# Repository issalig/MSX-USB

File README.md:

# MSX-USB
## My fork and DIY guide
My fork provides a minified version of the pcb with PLC sockets and a header expansion as well as detailed building guide. All the other things are the same as original S0urceror version (https://github.com/S0urceror/MSX-USB) and I send him lots of thanks for sharing his knowledge.

As I built the cartridge from the scratch I will tell you some of the problems I faced and happily solved out.

### Step 0: Make a PCB
When I saw original S0urceror design I thought that maybe using PLC sockets could make the pcb smaller, then I tried to shrink everything into the minimum space with the maximum capabilities and that's why I added a expansion header. I am using https://www.kicad.org/ for the PCB layout and https://freerouting.org/ for the routing. I find freerouting extremely useful since there are a lot of connections and a small place to do the job. Sometines freerouting does not find the solution and you need to finish it manually. If this happens you can also lower clearance matrix values down to 125-150. Also using freerouting allows you to change the location of components without the need to re-route everything again.

Last version of the pcb is kicad-cpld-mini-v2 (ch376 is in front but still *untested*) and kicad-cpld-mini (ch376 is in the back side and *tested ok*).  Of course if you are satisfied with my design just can just use the files provided. Otherwise you can improve the design and share it.

### Step 1: Program CPLD
You will need the obsolete part EPM7064SLC44, the important part here is **SLC**, EPM7064SLC44-10 is also valid. You can get them from ali and other places but as they are refurbished/recovered from dumpsters expect to have only 50% working, so order double. Here is a possible link https://aliexpress.com/item/1005001512009032.html but there is a myriad of sellers.
Then, you will need a programmer such as USB blaster. I got this one https://aliexpress.com/item/1005002674193901.html
Next, you have to download Quartus software version **13.0sp1**, as newer versions do not support EPM7064. Go to https://fpgasoftware.intel.com/?edition=lite and proceed with the download and installation.

If you are in linux like me you will  need to add the this rules to file /etc/udev/rules.d/37-usbblaster.rules
```
SUBSYSTEM=="usb", ATTRS{idVendor}=="09fb", ATTRS{idProduct}=="6001", GROUP="plugdev", MODE="0666", SYMLINK+="usbblaster" 
```
and then restart the service
```
sudo service udev restart 
```

Connect the programmer to the board and also **power the board externally with 5V**, you can do it using the expansion header or CH3786 header. Find the pins VCC and GND and you are done. Failing to do so it will result in an JTAG read error.

Next, we check your connection and if everything went ok you will see this message.
```
$ ./quartus_pgm --auto
Info (213045): Using programming cable "USB-Blaster [3-1]"
1) USB-Blaster [3-1]
  070640DD   EPM7064S

Info: Quartus II 32-bit Programmer was successful. 0 errors, 0 warnings
    Info: Peak virtual memory: 127 megabytes
    Info: Processing ended: Sat Dec 18 10:16:56 2021
    Info: Elapsed time: 00:00:00
    Info: Total CPU time (on all processors): 00:00:00
```

And it has arrived the amazing moment where you are going to program it (you can do it with the command line *quartus_pgm* or with the GUI tool *quartus*)
with the following file https://github.com/S0urceror/MSX-USB/blob/master/hardware/quartus/output_files/MSXUSB.pof
```
./quartus_pgm -m jtag -o "p;./MSXUSB.pof"
```

In case the devices still shows JTAG communication error, keep calm and go to the next step.

### Step 1b. Recovering deaf JTAG units
It happens that some of the refurbished units come with programs that used JTAG pins for I/O and they are not able to be used for JTAG. I threw some of them to the bin until I discovered a recovery process (https://www.eevblog.com/forum/fpga/atmel-atf150x-cpld-and-wincupl/msg3162224/#msg3162224).
- Apply 12V to CPLD pin OE1 (44) with a 2k2 resistor for a minute or so. In my pcb you can access OE1 pin on header pin 15 (RST).
- Disconnect 12V, connect 5V and try to program it.
- Hopefully some CPLD's are working now! 

### Step 1c. Use an still in production CPLD, use a ATF1504AS
As seen in https://www.eevblog.com/forum/fpga/atmel-atf150x-cpld-and-wincupl/msg3113922/#msg3113922 ATF1504AS is pin compatible to EPM7064 and it is a valid replacement for EPM7064.
The changes are not that big: we will need to convert .pof into .jed and then into .svf.

I compiled the following info from different sources https://github.com/marqs85/snes_dejitter/blob/master/README.md, https://github.com/SukkoPera/OpenAmiga500FastRamExpansion/blob/master/firmware/README.md and https://www.hackup.net/2020/01/erasing-and-programming-the-atf1504-cpld/

All the resources for ATMEL CPLDS can be found at https://www.microchip.com/en-us/products/fpgas-and-plds/spld-cplds/pld-design-resources

First we need to download pof2jef from http://ww1.microchip.com/downloads/archive/pof2jed.zip
Then in winpof2jed.exe (yes it works with wine in linux :))
```
1. Select .pof file from previous step as input file
2. Select 1504AS as device
3. Change the following options:
  * Reduce MC power -> On
  * Open Collector -> Off
  * JTAG mode -> On
  * Slew rate -> Slow
4. Click "Run"
```

The important thing here is JTAG Mode **ON**, if you are wrong you will block JTAG but don't panic, we already know that applying 12V it will be enabled again.

Once we have the .jed file it is time to generate svf with ATMISP that you can download it from http://ww1.microchip.com/downloads/en/DeviceDoc/ATMISP7.zip. Then, you should follow these steps.

```
1. Create a new device chain via File->New
2. Set number of devices to 1
3. Set device to ATF1504AS
4. Set JTAG instruction to "Program/Verify"
5. Select .jed file from previous step as JEDEC file
6. Name your svf file
7. Click "OK"
8. Tick "Write SVF file" and click "Run"
```

We are almost there. We just need to flash it with openocd

But first we need the config file for usbblaster and you can save it as altera-usb-blaster.cfg
```
#
# Altera USB-Blaster
#
# http://www.altera.com/literature/ug/ug_usb_blstr.pdf
#

interface usb_blaster
usb_blaster_lowlevel_driver ftdi
# These are already the defaults.
# usb_blaster_vid_pid 0x09FB 0x6001
# usb_blaster_device_desc "USB-Blaster"
adapter_khz 3000
```

And this is the magical line that will flash your CPLD (Do not forget to power usbblaster with external 5V)

```
 openocd -f altera-usb-blaster.cfg -c "adapter_khz 400" -c "transport select jtag" -c "jtag newtap ATF1504AS tap -irlen 3 -expected-id 0x0150403f" -c init -c "svf msxusb.svf" -c "sleep 200" -c shutdown
 ```
 
If everything went ok you will see something ending like this

```
Time used: 0m12s613ms 
svf file programmed successfully for 3299 commands with 0 errors
shutdown command invoked

```

### Step 2. Flash memory
Recommended memory chips is SST39SF040 (512kb) but I also managed to make it work with SST39SF020 (256kb). Then, you will need a programmer such as TL866 II https://aliexpress.com/item/33000308958.html and the file we will write is located at https://github.com/S0urceror/MSX-USB/blob/master/drivers/NextorUsbHost/dist/nextor.rom

If you prefer to use a command line tool I suggest you minipro https://gitlab.com/DavidGriffith/minipro

```
$ ./minipro --device SST39SF040@PLCC32 --write nextor.rom -s
Found TL866II+ 04.2.126 (0x27e)
Warning: Firmware is newer than expected.
  Expected  04.2.124 (0x27c)
  Found     04.2.126 (0x27e)
Chip ID OK: 0xBFB7
Warning: Incorrect file size: 131072 (needed 524288)
Erasing... 0.40Sec OK
Writing Code...  26.38Sec  OK
Reading Code...  4.00Sec  OK
Verification OK

```

### Step 3. Select a valid USB drive
Not all USB drives will work :(, I have detected that the ones with the following EnpointAddress values usually work. It will probably work if you have the values shown below. If you find other values, please report.
```
lsusb -v | grep bEndpointAddress
...
bEndpointAddress 0x01 EP 1 OUT
bEndpointAddress 0x82 EP 2 IN 
```

### Step 4. Prepare a disk
Once we are here, all the hardware requirements are fulfilled, yes, you can go for a beer now!
It is only a matter of creating a disk image with the system files provided at https://github.com/S0urceror/MSX-USB/tree/master/software/dist

- If you have a MSX1 (i.e. VG8020, ...) you will be limited to 720kb disks and FAT12. Do not complain, do you still prefer a slow datacorder?
To create a MSX disk image I use dsktool from https://github.com/nataliapc/MSX_devs/tree/master/dsktool

I also provide linux and windows version of dsktool in order to make it easier, you can get them at https://github.com/issalig/MSX-USB/tree/master/software/utils
```
#create disk
dsktool c MYDISK.DSK
#add system files
dsktool a MYDISK.DSK COMMAND.COM MSXDOS.SYS
#add other files
dsktool a MYDISK.DSK MYGAME.COM
```
In case you prefer a GUI program you can also use DiskMgr http://www.lexlechz.at/en/software/DiskMgr.html

Next, flash it. **Warning: check if your device is /dev/sda** or you will destroy something. If you are a windows user maybe Rufus can write the image, if it works, please report it. 

```
sudo dd if=MYDISK.DSK of=/dev/sda
```

- If you are a lucky MSX2 owner you will need a FAT16 partition of 16Mb with COMMAND2.COM and NEXTOR.SYS.

In Linux I have created an image available at https://github.com/issalig/MSX-USB/blob/master/software/utils/msx2.zip. You can do it with the following commands.
```
#create a 16 Mb disk and format it to FAT16
sudo  dd if=/dev/zero of=msx2.dsk bs=1024 count=16k
sudo mkfs.fat -F 16 msx2.dsk

#mount it
mkdir 16mb 
sudo mount -o loop msx2.dsk 16mb/

#copy all the stuff
sudo cp COMMAND2.COM NEXTOR.SYS 16mb

#unmount it and flash it
sudo umount 16mb
sudo dd if=msx2.dsk of=/dev/sda bs=16M
```
Unplug the stick from the computer, plug it in the msxusb, switch on the MSX and you are in. **Enjoy!**

As usual report how is it done with windows (maybe mini partition tool can help but I have never tried it).

## Some history
In the 80's the MSX standard was created by Kazuhiko Nishi. He envisioned a simple yet powerful home computer based on standard hardware, software (BIOS/MSX DOS) and connectivity. From 1983 to 1990 manufacturers, like Philips, Sony, Yamaha, Sharp, Canon and many more, made computers according to this standard.

Because of the fact that extensibility was part of the standard people could design cartridges that would add synthesizer sound, memory, modems, rom-based games, or combinations of the above.

Cartridges were connected via a standard 50pin connector that remained the same accross 4 generations of MSX (1/2/2+/TurboR). BIOS and MSX-DOS were designed in a way to discover these via rom-based drivers, software hooks, extended bios.

Standardisation offers a big advantage because everything that adheres to the standard can connect to it.

## USB
USB was designed in the 90's to do something similar. To standardize the connection of peripherals to personal computers, both to communicate with and to supply electric power. It has now largely replaced interfaces such as serial ports and parallel ports, and has become commonplace on a wide range of devices. Like USB flash drives, keyboards, mice, wifi, serial, camera's, etc.

What if the MSX would have an USB connection? And if the BIOS/MSX DOS would automatically recognize devices connected to it?

## Meet MSX-USB
Inspired by the work of Xavirompe and his [RookieDrive](http://rookiedrive.com/en/) I set out to do exactly this. And since I'm a big believer of open standards and open source I'm opening up my work to everyone.

On this GitHub page you can find:
* Schematics (KiCAD), that interfaces a cheap USB CH376s board to the MSX cartridge port.
* Drivers, currently Flash drives on Nextor and HID keyboards are supported.
* Debugging tools, to connect a test board to your PC/MAC and assist in debugging.

On my GitHub I also have forks of OpenMSX and CocoaMSX that either emulate or connect to a test board via serial to assist in development and debugging.

## Schematics
This connects the CH376s board you can find on eBay or AliExpress for around 4 Euro to the MSX. 

Circuitry is added to correctly handle the _BUSDIR signal. Make sure you select parallel by setting the jumper on the CH376s board correctly.

The CH376s board will be visible on port 10h and 11h on the MSX. Port 11h is the command port and 10h is the data port. Specifics on how to program for the CH376s are scattered around the Internet:
* https://www.mpja.com/download/ch376ds1.pdf
* https://arduinobasics.blogspot.com/2015/05/ch376s-usb-readwrite-module.html

Most information is available on how to use the higher-order API for flash drives. 

If you want to use other USB devices you have to go low-level. As it turns out Konamiman already did some work there and after some researching I got USB HID Keyboards, Ethernet, Serial working as well. Check out my source-code or these great pages for more information:
* http://www.usbmadesimple.co.uk/index.html
* https://www.beyondlogic.org/usbnutshell/usb1.shtml

## UNAPI USB
I wrote a UNAPI USB specification and implemented the Usb Host driver according to this. The next version of this Host driver will also implement the Usb Hub specification and enumerate and initialise all devices connected.

## USB HID Keyboard
The Usb Keyboard driver connects to Unapi Usb driver and hooks itself to H.CHGE. From that moment on it replaces your trusted MSX keyboard by a shiny new USB Keyboard. Or a wireless one if you have inserted the appropriate Logitech receiver.

## USB CDC ECM Ethernet
The USB CDC ECM Ethernet driver is finished. It uses the Unapi USB and conforms to the Unapi Ethernet standard. Internestor Lite can now connect and use your USB Ethernet device. Please note that currently we only support USB CDC ECM. Make sure your Ethernet device supports this.

All USB Ethernet devices built around the **RTL8153** chipset support USB CDC ECM. They usually cost around 20 euro.

## USB Storage
A low level USB driver is created to connect to storage devices like thumb drives, portable hard disks, etc. 

## USB Hub
The USB Hub driver will interrogate an USB Hub and all devices connected to it.

# Installation instructions
Check [this page](INSTALL.md) for installation instructions and links to the various binaries that have been developed.

# Build your own (DIY)
Check [this page](DIY.md) for information on how to make the PCB, program the CPLD device, flash the ROM, etc.

# Collaboration
Do you want to help with the development of MSX USB? Write drivers for other devices? Or contribute in other ways?

Please drop me line on sourceror at neximus.nl or meet me on the msx.org forum.

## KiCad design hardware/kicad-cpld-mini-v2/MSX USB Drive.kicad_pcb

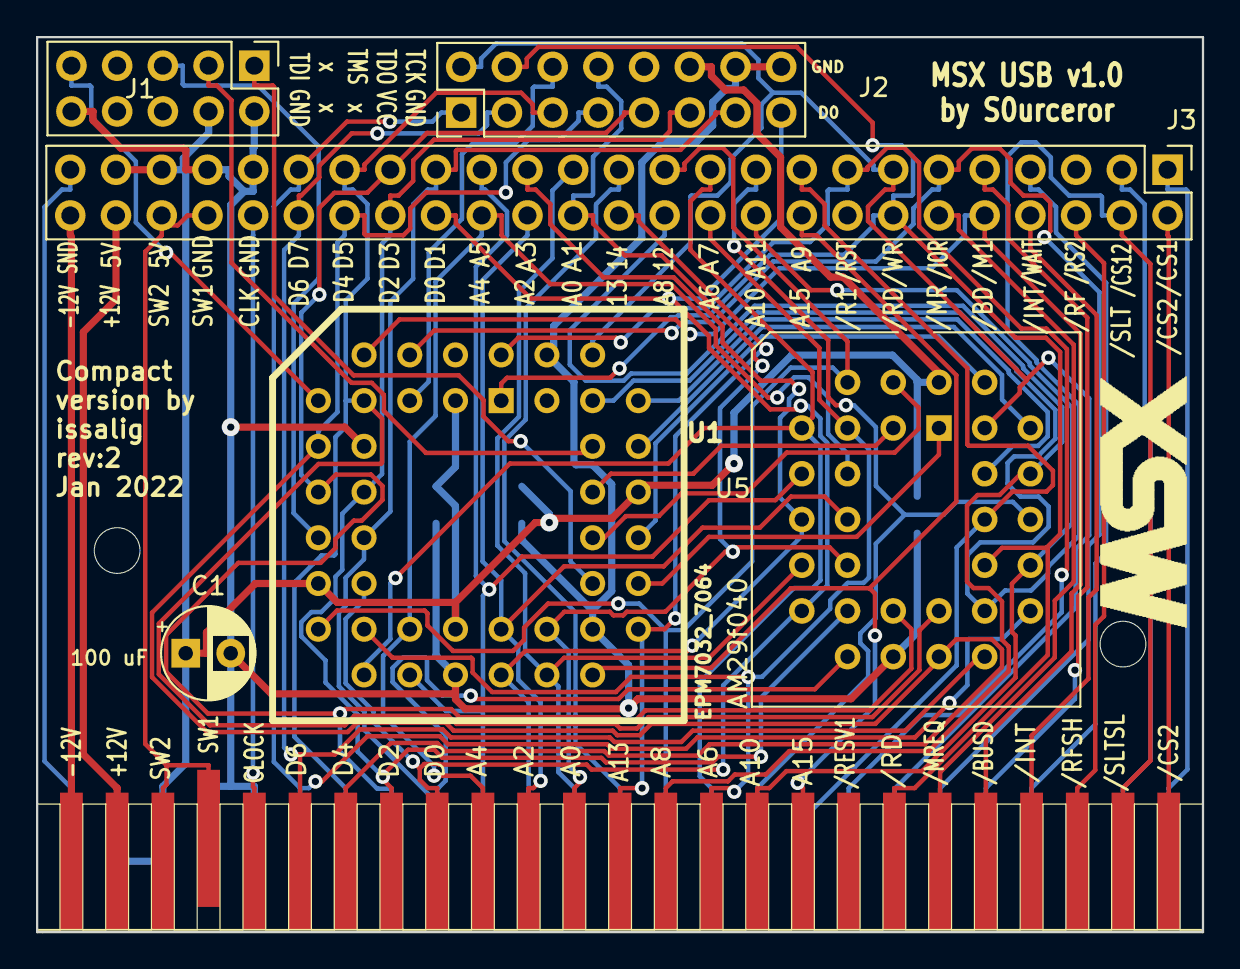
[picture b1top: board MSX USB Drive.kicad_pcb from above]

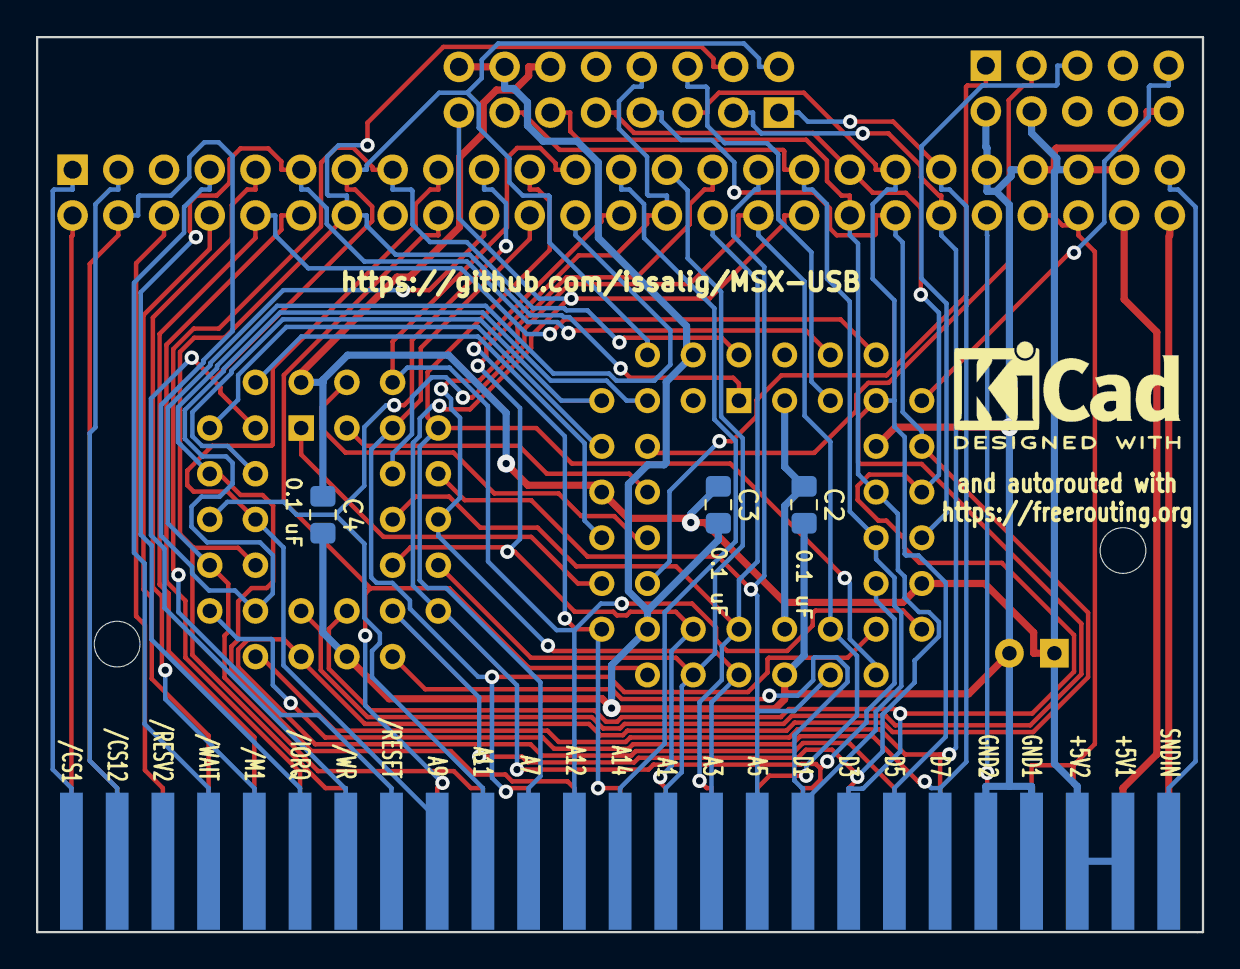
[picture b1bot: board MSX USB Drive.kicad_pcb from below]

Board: 2 copper layers, 64.8 x 49.7 mm, 11 parts (3 on the bottom side), 56 nets.

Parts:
C1: 100 uF; CP_Radial_D5.0mm_P2.50mm
C2, C3, C4: 0.1 uF; C_0805_2012Metric_Pad1.15x1.40mm_HandSolder
EDG1: MSX_CON; msx-con-MSXCART
J1: AVR-JTAG-10; PinHeader_2x05_P2.54mm_Vertical
J2: Conn_02x08_Odd_Even; PinHeader_2x08_P2.54mm_Vertical
J3: Conn_02x25_Odd_Even; PinHeader_2x25_P2.54mm_Vertical
LOGO_MSX: LOGO_MSX
U1: EPM7032_7064; PLCC44
U5: AM29f040; PLCC-32_THT-Socket

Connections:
+12V: EDG1.+12V, J3.48
-12V: EDG1.-12V, J3.50
A0: EDG1.A0, J2.8, J3.28, U1.27, U5.12
A1: EDG1.A1, J3.27, U1.26, U5.11
A2: EDG1.A2, J3.30, U1.25, U5.10
A3: EDG1.A3, J3.29, U1.24, U5.9
A4: EDG1.A4, J3.32, U1.21, U5.8
A5: EDG1.A5, J3.31, U1.20, U5.7
A6: EDG1.A6, J3.22, U1.19, U5.6
A7: EDG1.A7, J3.21, U1.18, U5.5
A8: EDG1.A8, J3.24, U5.27
A9: EDG1.A9, J3.17, U5.26
A10: EDG1.A10, J3.20, U5.23
A11: EDG1.A11, J3.19, U5.25
A12: EDG1.A12, J3.23, U1.17, U5.4
A13: EDG1.A13, J3.26, U1.29
A14: EDG1.A14, J3.25
A15: EDG1.A15, J3.18, U1.28
BUSDIR_: EDG1./BUSDIR, J3.10, U1.6
CLOCK: EDG1.CLOCK, J3.42
CS1: EDG1./CS1, J3.1
CS2: EDG1./CS2, J3.2
CS12: EDG1./CS12, J3.3
CS_: J2.6, U1.5
D0: EDG1.D0, J2.15, J3.34, U1.16, U5.13
D1: EDG1.D1, J2.13, J3.33, U1.14, U5.14
D2: EDG1.D2, J2.11, J3.36, U1.12, U5.15
D3: EDG1.D3, J2.9, J3.35, U1.11, U5.17
D4: EDG1.D4, J2.7, J3.38, U1.9, U5.18
D5: EDG1.D5, J2.5, J3.37, U1.8, U5.19
D6: EDG1.D6, J2.3, J3.40, U5.20
D7: EDG1.D7, J2.1, J3.39, U5.21
GND: C1.2, C2.2, C3.2, C4.2, EDG1.GND1, EDG1.GND2, J1.2, J1.10, J2.14, J2.16, J3.41, J3.43, U1.10, U1.22, U1.30, U1.42, U5.16
INT: EDG1./INT, J3.8
IORQ_: EDG1./IORQ, J3.11, U1.4
M1: EDG1./M1, J3.9
MA13: U1.39, U5.28
MA14: U1.37, U5.29
MA15: U1.36, U5.3
MA16: U1.34, U5.2
MA17: U1.33, U5.30
MA18: U1.31, U5.1
MREQ: EDG1./MREQ, J3.12
RD_: EDG1./RD, J2.4, J3.14, U1.1, U5.24
RESET_: EDG1./RESET, J3.15, U1.44
RFSH: EDG1./RFSH, J3.6
SLTSL_: EDG1./SLTSL, J3.4, U1.41, U5.22
SOUNDIN: EDG1.SOUNDIN, J3.49
SW1: EDG1.SW1, EDG1.SW2, J3.44, J3.46
TCK: J1.1, U1.32
TDI: J1.9, U1.7
TDO: J1.3, U1.38
TMS: J1.5, U1.13
VCC: C1.1, C2.1, C3.1, C4.1, EDG1.+5V1, EDG1.+5V2, J1.4, J2.12, J3.45, J3.47, U1.3, U1.15, U1.23, U1.35, U5.32
WAIT: EDG1./WAIT, J3.7
WR_: EDG1./WR, J2.2, J3.13, U1.40, U5.31

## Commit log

2021-12-24 win tool
2021-12-24 dsktool linux
2021-12-24 dsktool
2021-12-26 new board with front ch376 and pinout in silkscreen
2021-12-26 msx2 disk image with 16mb and fat16
2021-12-26 updated msx2 disk
2022-01-04 atf1504as instructions
